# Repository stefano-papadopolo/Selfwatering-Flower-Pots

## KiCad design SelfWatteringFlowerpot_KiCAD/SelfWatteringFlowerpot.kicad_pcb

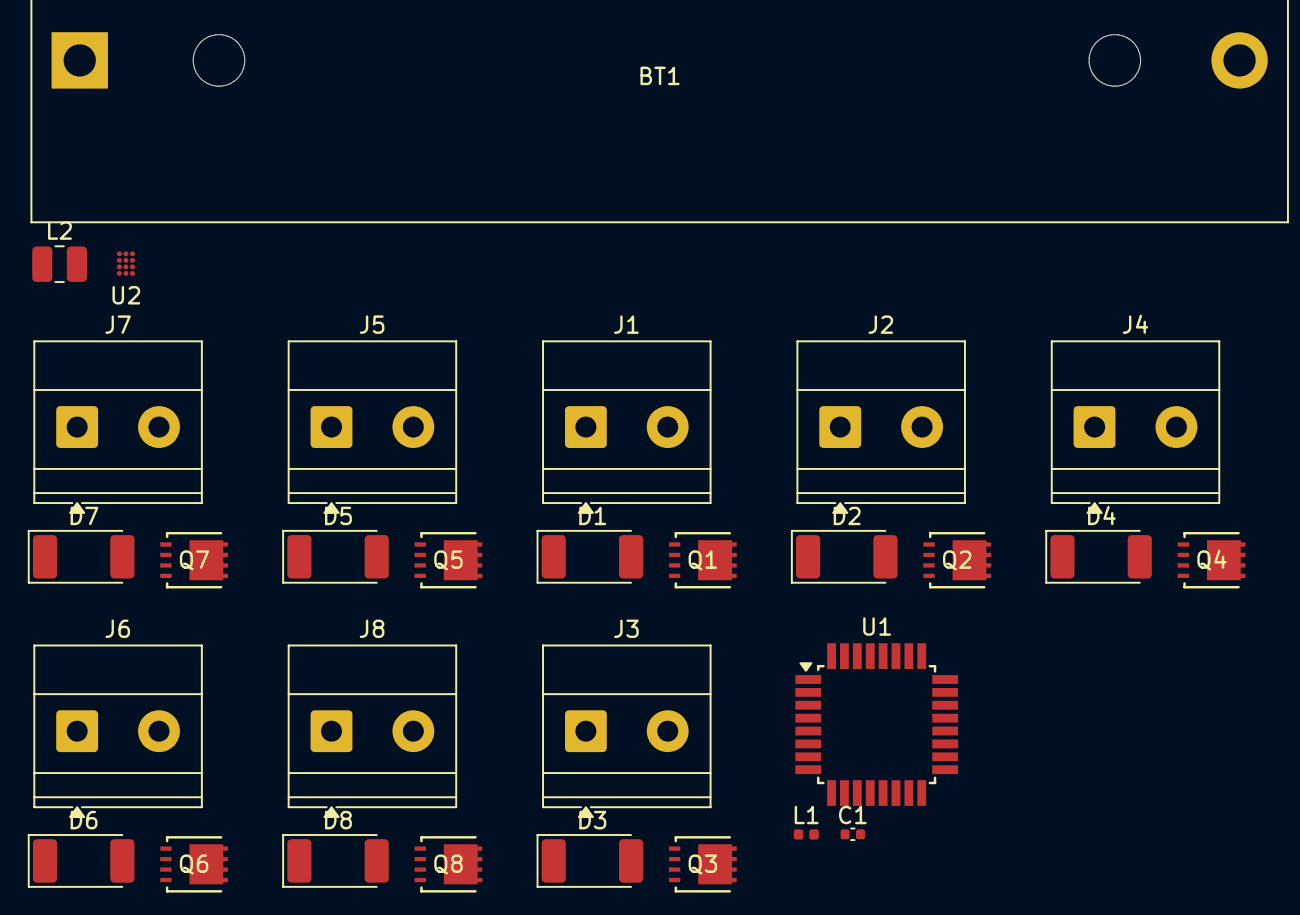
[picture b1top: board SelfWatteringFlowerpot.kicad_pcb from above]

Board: 2 copper layers, 30 parts (0 on the bottom side), 24 nets, no tracks yet.

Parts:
BT1: 3.7V; BatteryHolder_MPD_BH-18650-PC2
C1: 100nF; C_0402_1005Metric
D1, D2, D3, D4, D5, D6, D7, D8: SM5059; D_MELF
J1, J2, J3, J4, J5, J6, J7, J8: Conn_01x02; TerminalBlock_Phoenix_MKDS-1,5-2-5.08_1x02_P5.08mm_Horizont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
L1: 10mH; L_0402_1005Metric
L2: 1.5uH; L_1008_2520Metric
Q1, Q2, Q3, Q4, Q5, Q6, Q7, Q8: XPN7R104NC_L1XHQ; TSON_AdvanceWF_TOS
U1: ATtiny828-A; TQFP-32_7x7mm_P0.8mm
U2: BD83070GWL-E2; UCSP50L1C_ROM

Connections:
/Pump1/SIGNAL: Q1.4 (GATE), U1.9 (PA0)
/Pump2/SIGNAL: Q2.4 (GATE), U1.10 (PA1)
/Pump3/SIGNAL: Q3.4 (GATE), U1.11 (PA2)
/Pump4/SIGNAL: Q4.4 (GATE), U1.12 (PA3)
/Pump5/SIGNAL: Q5.4 (GATE), U1.13 (PA4)
/Pump6/SIGNAL: Q6.4 (GATE), U1.14 (PA5)
/Pump7/SIGNAL: Q7.4 (GATE), U1.15 (PA6)
/Pump8/SIGNAL: Q8.4 (GATE), U1.16 (PA7)
GND: BT1.2 (-), D1.2 (A), D2.2 (A), D3.2 (A), D4.2 (A), D5.2 (A), D6.2 (A), D7.2 (A), D8.2 (A), J1.2, J2.2, J3.2, J4.2, J5.2, J6.2, J7.2, J8.2, U1.5 (GND), U1.21 (GND), U2.A2 (GND), U2.D2 (PGND)
unnamed: BT1.1 (+), U2.A1 (EN), U2.B2 (Mode), U2.C3 (PVIN)
unnamed: C1.1, L1.2
unnamed: D1.1 (K), J1.1, Q1.1 (SOURCE), Q1.2 (SOURCE), Q1.3 (SOURCE)
unnamed: D2.1 (K), J2.1, Q2.1 (SOURCE), Q2.2 (SOURCE), Q2.3 (SOURCE)
unnamed: D3.1 (K), J3.1, Q3.1 (SOURCE), Q3.2 (SOURCE), Q3.3 (SOURCE)
unnamed: D4.1 (K), J4.1, Q4.1 (SOURCE), Q4.2 (SOURCE), Q4.3 (SOURCE)
unnamed: D5.1 (K), J5.1, Q5.1 (SOURCE), Q5.2 (SOURCE), Q5.3 (SOURCE)
unnamed: D6.1 (K), J6.1, Q6.1 (SOURCE), Q6.2 (SOURCE), Q6.3 (SOURCE)
unnamed: D7.1 (K), J7.1, Q7.1 (SOURCE), Q7.2 (SOURCE), Q7.3 (SOURCE)
unnamed: D8.1 (K), J8.1, Q8.1 (SOURCE), Q8.2 (SOURCE), Q8.3 (SOURCE)
unnamed: C1.2, U1.18 (AVCC)
unnamed: L1.1, U1.4 (VCC)
unnamed: L2.1, U2.D3 (LX1)
unnamed: L2.2, U2.D1 (LX2)
Out_12VReg: Q1.5 (DRAIN), Q1.6 (DRAIN), Q1.7 (DRAIN), Q1.8 (DRAIN), Q2.5 (DRAIN), Q2.6 (DRAIN), Q2.7 (DRAIN), Q2.8 (DRAIN), Q3.5 (DRAIN), Q3.6 (DRAIN), Q3.7 (DRAIN), Q3.8 (DRAIN), Q4.5 (DRAIN), Q4.6 (DRAIN), Q4.7 (DRAIN), Q4.8 (DRAIN), Q5.5 (DRAIN), Q5.6 (DRAIN), Q5.7 (DRAIN), Q5.8 (DRAIN), Q6.5 (DRAIN), Q6.6 (DRAIN), Q6.7 (DRAIN), Q6.8 (DRAIN), Q7.5 (DRAIN), Q7.6 (DRAIN), Q7.7 (DRAIN), Q7.8 (DRAIN), Q8.5 (DRAIN), Q8.6 (DRAIN), Q8.7 (DRAIN), Q8.8 (DRAIN)

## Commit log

2025-05-29 Changed Kicad folder Name
2025-06-04 Created Basics submodule
